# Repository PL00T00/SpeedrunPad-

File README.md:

# SpeedrunPad-
A simple 4 key hack pad that can be used for minecraft speedrunning. Also includes a rotary encoder to quickly change on of your settings.

I made this project cause ive recently started to get into the Minecraft speedrunning community and having a dedicated macropad for it justsounds really cool!

Here's my PCB!

Here's a 3d model of it all!

And here's my schematic!

The parts this macropad uses are
- 4x switches
- 1x xiao rp2040
- 1x EC11 rotary encoder
- 4x Keycaps
- 4x SK6812 MINI-E LEDs
- 4x M3x16mm screws
- 4x M3x5mx4mm heatset inserts
- 1x pcb
- 1x 3d printed case

Funding requested - 15USD for case and PCB

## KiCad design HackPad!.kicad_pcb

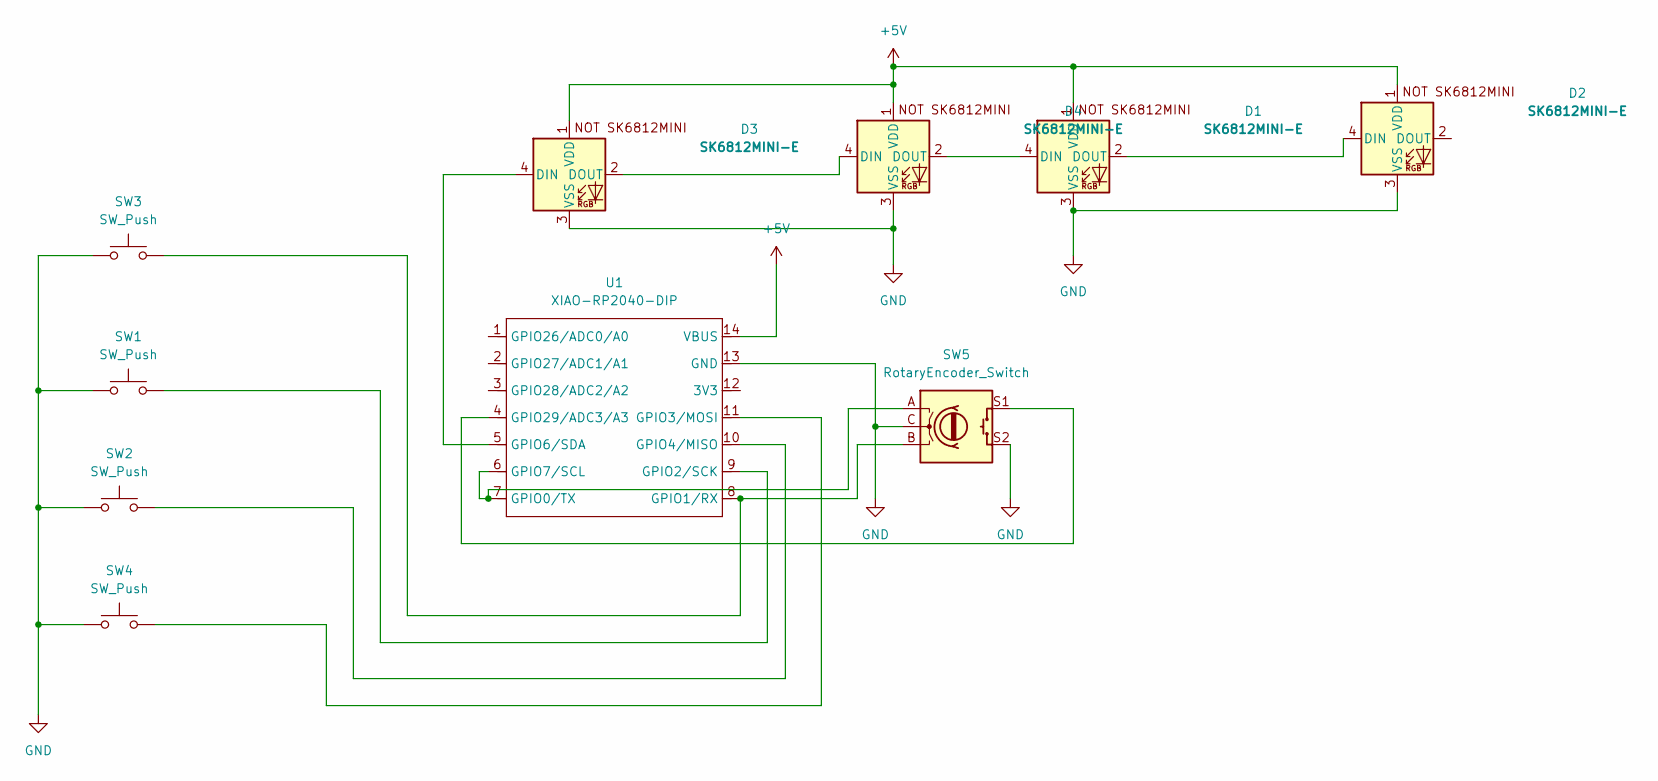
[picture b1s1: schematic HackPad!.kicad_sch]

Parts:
D1, D2, D3, D4: SK6812MINI-E; MX_SK6812MINI-E_REV
SW1, SW2, SW3, SW4: SW_Push; SW_Cherry_MX_1.00u_PCB
SW5: RotaryEncoder_Switch; RotaryEncoder_Alps_EC11E-Switch_Vertical_H20mm
U1: XIAO-RP2040-DIP

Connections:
+5V: D1.1 (VDD), D2.1 (VDD), D3.1 (VDD), D4.1 (VDD), U1.14 (VBUS)
GND: D1.3 (VSS), D2.3 (VSS), D3.3 (VSS), D4.3 (VSS), SW1.1, SW2.1, SW3.1, SW4.1, SW5.C, SW5.S2, U1.13 (GND)
unnamed: D1.4 (DIN), D4.2 (DOUT)
unnamed: D1.2 (DOUT), D2.4 (DIN)
unnamed: D3.4 (DIN), U1.5 (GPIO6/SDA)
unnamed: D3.2 (DOUT), D4.4 (DIN)
unnamed: SW5.A, U1.6 (GPIO7/SCL), U1.7 (GPIO0/TX)
unnamed: SW3.2, SW5.B, U1.8 (GPIO1/RX)
unnamed: SW1.2, U1.9 (GPIO2/SCK)
unnamed: SW4.2, U1.11 (GPIO3/MOSI)
unnamed: SW2.2, U1.10 (GPIO4/MISO)
unnamed: SW5.S1, U1.4 (GPIO29/ADC3/A3)

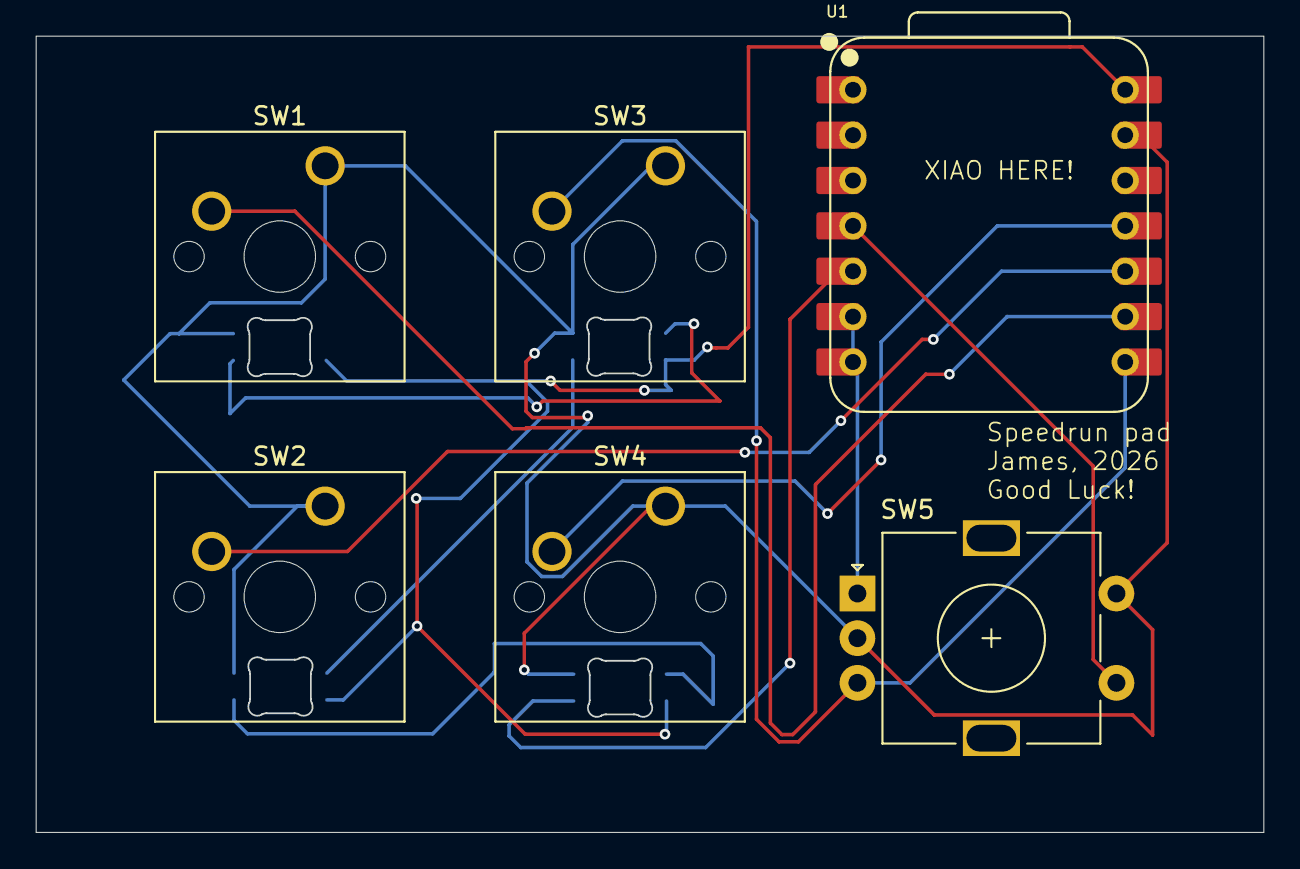
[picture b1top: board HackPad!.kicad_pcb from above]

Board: 2 copper layers, 68.7 x 44.5 mm, 10 parts (0 on the bottom side), 12 nets.

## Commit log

2026-01-24 case done
2026-01-24 Update README to include rotary encoder feature
2026-01-25 Enhance README with project motivation and image
    Added personal motivation and PCB image to README.
2026-01-25 Add initial firmware setup for keyboard with encoders
2026-01-26 Remove 'g' from README file
2026-01-26 Create PLACEHOLDER
2026-02-01 Add 3D model image to README
    Added a 3D model image of the PCB.
